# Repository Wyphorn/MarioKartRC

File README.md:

# Mario Kart RC

Mario-Kart-inspiriertes RC-Rennsystem für 8 Fahrzeuge im Außeneinsatz. Die Autos fahren mit ~20 km/h; Items, Kollisionen und Rundenzählung werden automatisch erkannt.

Das Projekt ist auf Nachbau ausgelegt: Alle Bauteile haben eine feste Bestellnummer eines echten Herstellers mit öffentlichem Datenblatt und sind handlötbar (SOT-23, SOT-223, SMA, THT – kein QFN).

---

## Repo-Struktur

| Ordner | Inhalt |
|---|---|
| `fb-firmware/` | Fernbedienung – ESP32-C6-SuperMini, PlatformIO |
| `car-firmware/` | Fahrzeug – ESP32-C6 Mini, PlatformIO |
| `shared/` | Gemeinsamer Code: `mk_protocol.h` (Pakete FB ↔ Auto ↔ Basis), `mk_clock_guard.h` (Workaround für den C6-Uhrenfehler) |
| `kicad/projects/` | KiCad-Projekte je Platine: `kart` (Fahrzeug-Board), `controller` (Fernbedienung), `buttons` (Tasterplatine FB), `switch` (Schalter-Platinchen Kart), jeweils mit Gerber als ZIP |
| `kicad/libs/` | Eigene Symbole und Footprints (`zzzz_Own`, `RF_Module_Own`), von allen Projekten über ihre lokalen Bibliothekstabellen eingebunden |
| `kicad/archive/` | Alte Stände: FB-V1-Layout, erster FB-Schaltplan (D1 Mini, Mai 2026) |
| `docs/` | Weitere Dokumentation, u.a. `base-station.md` |

---

## Gesamtarchitektur

| Bereich | Technologie |
|---|---|
| Drahtlos | ESP-NOW |
| Kabelgebunden | CAN-Bus (STM32F103 + TJA1050) |
| Basisstation | Raspberry Pi 5 + USB-CAN-Adapter |
| Fahrzeugbasis | Carrera 2013 RC-Autos (umgebaut) |
| Fahrzeug-MCU | ESP32-C6 Mini |
| Fernbedienung | ESP32-C6-SuperMini (gleicher Chip wie im Auto) |

**Faustregel:** kabelgebunden = CAN, drahtlos = ESP-NOW.

---

## Betriebs-Modi

**Direct Mode** – Die Fernbedienung (FB) steuert ihr Auto direkt. Keine Basisstation nötig, ideal zum Einzelfahren und Testen.

**Game Mode** – Die FB spricht mit der Basisstation. Diese übernimmt die Spiellogik (Items, Punkte, Kollisionen, Rundenzählung) und leitet die Fahrbefehle ans Auto weiter.

Gewählt wird der Modus mit dem Schiebeschalter der FB: Mitte = Aus, Links = Game, Rechts = Direct.

---

## Kommunikationsprotokoll (`shared/mk_protocol.h`)

Alle ESP-NOW-Pakete beginnen mit einem `uint8_t type` als Unterscheidungsmerkmal.

| Struct | Richtung | Frequenz |
|---|---|---|
| `MK_ControlInput` | FB → Auto (Direct) / FB → Basis (Game) | ~50 Hz |
| `MK_ConfigPacket` | FB → Auto / FB → Basis → Auto | nur bei Änderung |
| `MK_GameFeedback` | Auto → FB (Direct) / Basis → FB (Game) | 5 Hz |
| `MK_Beacon` | FB/Auto → Broadcast | beim Pairing |
| `MK_Assign` | Basis → FB/Auto (Unicast) | beim Pairing |
| `MK_ChannelSwitch` | Basis/FB → Auto | Kanalwechsel / Rennende |
| `MK_Mapping` | Basis → FB/Auto (Unicast) | vor Rennstart |
| `MK_IrConfig` | Basis → Auto (Unicast) | nach Assign (nur Game Mode) |

- **`MK_ControlInput`** – `throttle` und `steering` (–100..100), `buttons` (Bitmaske Gelb/Grün/Blau/Rot), `maxSpeed` (1–10)
- **`MK_ConfigPacket`** – Servo-Trim –10..10; `save = 1` speichert im Auto-EEPROM, `save = 0` ist eine Live-Vorschau
- **`MK_GameFeedback`** – Position, Runde, Item, Rumble, Akkustand des Autos (0–5) und sein aktueller Servo-Trim
- **`MK_Beacon`** – enthält beim Auto die Charakter-ID (1–8)

### Pairing und Wiederverbinden (Direct Mode)

1. Erstes Pairing auf dem Setup-Kanal 1: Das Auto sendet Beacons, die FB antwortet mit `MK_Assign` und schickt es per `MK_ChannelSwitch` auf einen zufälligen Betriebskanal (4, 6, 9 oder 11).
2. Beide speichern Kanal und Gegenstelle im EEPROM.
3. **Wiederverbinden ist FB-gesteuert:** Nach einem Neustart oder Funkabriss meldet sich die FB mit ihrer echten MAC auf dem gespeicherten Kanal beim gespeicherten Auto und sendet einfach Steuerpakete. Das Feedback des Autos bestätigt die Verbindung – kein Beacon, kein erneutes Assign.
4. Rückfall auf Kanal 1 erst, wenn die Gegenstelle wirklich weg ist: Auto nach 30 s Funkstille (5 s direkt nach dem Einschalten), FB nach 30 s (15 s nach dem Einschalten). Kanal 1 wird bewusst vermieden, weil dort die erste FB gewinnt und die Zuordnung FB ↔ Auto wechseln könnte.

---

## Fernbedienung

### Hardware

| Komponente | Details |
|---|---|
| MCU | ESP32-C6-SuperMini (MakerGO) |
| Joysticks | 2× PS2-Analog-Stick, direkt an 3.3V (kein Spannungsteiler) |
| ADC | ADS1115 als Breakout-Modul, I2C 0x48 (ADDR → GND) |
| Display | 1.9" IPS 170×320, ST7789, SPI |
| Buttons | 4× Taster (SNES-Raute) + 2× Stick-Taster (verdrahtet, ohne Funktion) |
| Status-LED | WS2812B, 330 Ω Serienwiderstand |
| Rumble | 2× ERM-Vibrationsmotor 28×12 mm, parallel an Zellspannung |
| Rumble-Treiber | 1× MMBT2222A + 1 kΩ Basis, 1× SS14 Freilaufdiode |
| Akku | 1× 18650, ungeschützt – zum Laden herausnehmen (externes Ladegerät) |
| Verpolschutz | P-MOSFET DMG2301L-7 (Ersatz: DMG2301LK-7), direkt hinter dem Akku |
| Spannungsregler | LDO MCP1826T-3302E/DC, fest 3.3V, 1 A |
| Power/Modus | Schiebeschalter 2P3T: Pol A schaltet SHDN des LDO, Pol B den Modus-Pin |
| Akku-Messung | Teiler 100k/100k + 100 nF an GPIO0 |
| Puffer | 220 µF Elko an der Akkuschiene (Rumble-Anlaufstrom) |

Alle Verbraucher außer dem Rumble laufen an einer einzigen 3.3V-Schiene.

> **Hinweis für Nachbauer:** Auf FB-Board V1 ist die Freilaufdiode D2 im Footprint verdreht. Den Kathodenring entgegen dem Siebdruck auf Pad 2 (+BATT) setzen – das ist die Seite mit Durchgang zu Pin 1 von J6/J7.

### Pinbelegung ESP32-C6-SuperMini

| GPIO | Funktion |
|---|---|
| GPIO0 | ADC – Akku-Messung |
| GPIO1 | Modus-Pin (Game = GND, Direct = 3.3V) |
| GPIO2 | Button Rot |
| GPIO3 | Button Blau |
| GPIO4 | Button Grün |
| GPIO5 | Display MOSI |
| GPIO6 | WS2812B DATA |
| GPIO7 | Display SCK |
| GPIO14 | Display Backlight (PWM) |
| GPIO15 | Display CS |
| GPIO17 | Rumble PWM |
| GPIO18 | Display DC |
| GPIO19 | I2C SDA (ADS1115) |
| GPIO20 | I2C SCL (ADS1115) |
| GPIO21 / 22 | Stick-Taster R / L (inneres Pad, reserviert) |
| GPIO23 | Button Gelb (inneres Pad, einzelner Draht) |

Tabu: GPIO8/9 (Strapping, Onboard-LED/BOOT), GPIO12/13 (USB zum Flashen und für den Serial-Monitor), GPIO16 (UART0 TX, wird vom Boot-ROM getrieben).

ADS1115-Kanäle: A0 = Links X, A1 = Links Y, A2 = Rechts Y, A3 = Rechts X (A2/A3 bewusst getauscht, damit sich die Leitungen nicht kreuzen).

### Tastenbelegung

```
        [Blau]
   [Grün]      [Rot]
        [Gelb]
```

| Taste | Im Menü | Beim Fahren |
|---|---|---|
| Grün | Bestätigen | – |
| Rot | Zurück / Abbrechen | Licht am Auto an/aus |
| Blau | – | Charakter-Sound |
| Gelb | – | – (frei) |
| Grün + Blau 3 s | – | Menü öffnen |
| Rot 10 s halten | – | Einstellungen zurücksetzen (Countdown ab 5 s) |
| Rot beim Einschalten | Einstellungen zurücksetzen | |

Standardbelegung der Sticks: links hoch/runter = Gas, rechts links/rechts = Lenkung (im Menü tauschbar).

### Status-LED

| Farbe | Bedeutung |
|---|---|
| Orange blinkend | sucht Auto bzw. Basis |
| Grün | verbunden |
| Orange | Akku unter 33 % |
| Rot blinkend | Akku unter 16 % |
| Pink | Menü offen |
| Gelb pulsierend / solid | Kalibrierung startet / läuft |

### Einstellungsmenü

| Menüpunkt | Gespeichert |
|---|---|
| Offset-Kalibrierung (Nullpunkt der Sticks) | FB |
| Min/Max-Kalibrierung (8 geführte Schritte) | FB |
| Servo-Trim (±10, Räder bewegen sich live mit, Grün speichert, Rot verwirft) | Auto |
| Max. Speed (1–10) | – |
| Sprache (DE/EN) | FB |
| Rumble an/aus | – |
| Joysticks tauschen | – |
| Debug (Achsen, Buttons, Spannung, Kanal, MAC) | – |
| Reset | – |

Vor der ersten Fahrt **Offset-Kalibrierung** machen – sonst liegt der Nullpunkt der Sticks daneben und das Auto kriecht los.

### Akku

- 0 % = 3.4V, 100 % = 4.2V. Unter ~3.35V fällt der LDO aus der Regelung und die Joystick-Werte wandern – deshalb gilt die Zelle schon bei 3.4V als leer.
- **Tiefentladeschutz:** Liegt die Zelle 30 s unter 3.3V, zeigt die FB „Akku leer – bitte ausschalten“ und geht in Deep Sleep. Nur Aus- und Einschalten holt sie zurück. Ein Restverbrauch von wenigen mA bleibt; bei längerer Lagerung die Zelle herausnehmen.
- Nach 60 s ohne Eingabe wird das Display gedimmt.

---

## Fahrzeug

### Hardware

| Komponente | Details |
|---|---|
| MCU | ESP32-C6 Mini |
| Motortreiber | BTS7960 H-Brücke (IBT-2), 43 A Peak |
| Antrieb | 380er Bürstenmotor, 7.4V, Stallstrom ~8 A |
| Lenkservo | Multiplex MS-12022 MG DIGI, PWM 1050–1950 µs (mechanischer Puffer) |
| Audio | DFPlayer Mini (UART) – Sounds aus einem Ordner pro Charakter |
| IMU | LSM6DS3, I2C 0x6A – Kollisionserkennung |
| LEDs | WS2812B-Kette: Status-LED + 8er-Kreis im Charakterkopf |
| Beleuchtung | Front weiß + Heck rot, Rückfahrlicht weiß |
| IR-Sender | 3× IR-LED 940 nm nach unten (Mitte, ±8 cm) – Typ noch offen |
| Charakter-ID | 4-fach DIP-Schalter + Widerstandsleiter an einem ADC-Pin |
| Akku | 2× 18650 in Serie (2S), ungeschützt – zum Laden herausnehmen |
| Stromversorgung | 7.4V direkt an den BTS7960, 5V über Buck AP63205WU (C6, DFPlayer, LEDs, Servo) |
| Akku-Messung | Teiler 100k/47k an GPIO4 |

### Pinbelegung ESP32-C6 Mini

| GPIO | Funktion |
|---|---|
| GPIO0 | I2C SCL (LSM6DS3) |
| GPIO1 | I2C SDA (LSM6DS3) |
| GPIO2 | ADC – Charakter-ID |
| GPIO3 | IR-LED (über MMBT2222) |
| GPIO4 | ADC – Akku-Messung |
| GPIO5 | BTS7960 RPWM (10k Pulldown) |
| GPIO6 | BTS7960 LPWM (10k Pulldown) |
| GPIO7 | Servo PWM |
| GPIO14 | Rückfahrlicht |
| GPIO15 | Front- + Rücklicht |
| GPIO18 | UART1 TX → DFPlayer RX |
| GPIO19 | UART1 RX ← DFPlayer TX |
| GPIO20 | WS2812B DATA |

BTS7960 R_EN/L_EN fest an 5V. GPIO8/9 bleiben frei (Strapping: dürfen beim Reset nicht auf LOW gezogen werden).

### Charakter-Identifikation (DIP-Schalter)

10 kΩ nach 3.3V, dazu vier Widerstände (4.7k / 10k / 20k / 51k), je per DIP-Schalter nach GND. Der kleinste Abstand zwischen zwei Charakteren beträgt 254 mV.

| Charakter | DIP [4.7k 10k 20k 51k] | Spannung | SD-Ordner |
|---|---|---|---|
| Mario    | 1110 | 0.713V | 01 |
| Luigi    | 1000 | 1.055V | 02 |
| Yoshi    | 0110 | 1.320V | 03 |
| Bowser   | 0100 | 1.650V | 04 |
| DK       | 0011 | 1.946V | 05 |
| Peach    | 0010 | 2.200V | 06 |
| Toad     | 0001 | 2.759V | 07 |
| Rosalina | 0000 | 3.300V | 08 |

Wird der DIP-Schalter umgestellt, während das Auto nicht verbunden ist, spielt es zur Kontrolle den Erkennungssound des neuen Charakters.

### SD-Karte des DFPlayers

```
/01/  001.mp3, 002.mp3, …   ← Mario
/02/  …                     ← Luigi
…
/08/  …                     ← Rosalina
/09/  …                     ← Spiel-Sounds (Stern, Banane, …)
```

Welche Tracks fröhlich bzw. traurig sind, steht in den Arrays `kJoy_*` / `kSad_*` am Anfang von `car-firmware/src/main.cpp`.

### LEDs

| Index | Funktion |
|---|---|
| 0 | Status-LED |
| 1–8 | Charakter-Kreis (Regenbogen) |

| Status-LED | Bedeutung |
|---|---|
| Orange blinkend | sucht / Verbindung unterbrochen |
| Grün | verbunden |
| Gelb | Akku unter 3.3V/Zelle |
| Rot blinkend | Akku unter 3.2V/Zelle – Abschaltung steht bevor |

### Akku

**Tiefentladeschutz:** Liegt der Akku 30 s unter 6.4V (3.2V/Zelle), stoppt das Auto, spielt einen traurigen Sound und geht in Deep Sleep. Jede Messung zählt, auch unter Last; eine erholte Messung beim Gaswegnehmen setzt den Zähler zurück. So löst es im Rennen erst aus, wenn der Akku wirklich leer ist.

### Kollisionserkennung

LSM6DS3 im ±16g-Bereich. Bei einem Stoß über der Schwelle vibriert die gekoppelte FB 2 s lang, danach 3 s Pause. Die Schwelle steht zum Testen auf 1.5g und soll nach dem Fahrtest wieder auf ~6g.

---

## Firmware bauen und flashen

```bash
cd fb-firmware      # bzw. car-firmware
pio run -t upload
pio device monitor
```

`upload_port`/`monitor_port` in `platformio.ini` sind auf die Seriennummern der eigenen Boards festgelegt – für andere Boards anpassen oder entfernen. Geflasht wird über den eingebauten USB-Port des C6 (USB-Serial/JTAG).

Beide Firmwares nutzen eine OTA-taugliche Partitionstabelle (`default.csv`). Sie lässt sich nur per USB ändern, deshalb ist sie ab dem ersten Flash gesetzt.

### ESP32-C6 rev v0.2: Uhr springt zurück

Beim ESP32-C6 in Revision v0.2 fallen im Zeitgeber gelegentlich einzelne Bits aus, sobald Funk und ein I2C-Master gleichzeitig laufen – `millis()` springt dann um Sekunden bis Minuten zurück ([esp-idf #19036](https://github.com/espressif/esp-idf/issues/19036)). Die Firmware umgeht das mit `shared/mk_clock_guard.h`:

- `nowMs()` zählt über den FreeRTOS-Tick, der auf einem nicht betroffenen Zähler läuft. Im eigenen Code **immer `nowMs()` statt `millis()` verwenden.**
- Ein Guard-Task erkennt Rücksprünge und setzt die Systemuhr zurück auf Stand (Log-Zeile `[CLOCK]`).
- Der WLAN-Stromsparmodus ist abgeschaltet.

Die Revision zeigt `esptool.py chip_id` an.

---

## Streckeninfrastruktur und IR-System

| Komponente | Funktion |
|---|---|
| TSOP38238 | IR-Empfänger, 38 kHz, ±45° – in Toren und Bodenplatten |
| STM32F103 + TJA1050 | CAN-Controller + Transceiver in den Tor-Nodes |
| RPi 5 + USB-CAN | Basisstation / Spielserver |

**Weg eines Ereignisses:** Auto fährt über eine Bodenplatte → TSOP38238 erkennt die IR-ID → STM32 → CAN → RPi 5 → Spiellogik.

Pro Tor sitzen drei Empfänger (Mitte und ±8 cm) passend zu den drei IR-LEDs am Auto. Bei 20 km/h bleibt ein Erkennungsfenster von ~8 ms.

---

## Projektstatus

| Schritt | Status |
|---|---|
| Architektur, Komponentenwahl, Protokoll | ✅ |
| Auto-Firmware (ESP-NOW, Motor, Servo, LEDs, IMU, Sound, Akku-Schutz) | ✅ |
| FB-Firmware auf ESP32-C6 portiert (Display, Menü, ESP-NOW, Rumble, Akku-Schutz) | ✅ |
| Direct Mode Ende-zu-Ende (Pairing, Reconnect, Trim, Sound, Licht) | ✅ |
| KiCad: Kart-Board und FB-Board | ✅ |
| FB-Board V1 gefertigt und aufgebaut | ✅ |
| Race-Display (Charakter, Position, Runde, Item) | ⏳ |
| IR-LED auswählen, einbauen, 38-kHz-Modulation | ⏳ |
| Verpolschutz + Hauptschalter am Akkuhalter des Autos | ⏳ |
| FB-Board V2 (Diode gedreht, Basis-Pulldown, 0.5-mm²-Anschlüsse) | ⏳ |
| Gehäuse anpassen (Fusion 360) | ⏳ |
| Basisstation-Software (Raspberry Pi) | ⏳ |
| Game Mode Ende-zu-Ende | ⏳ |
| OTA-Update | ⏳ zurückgestellt bis nach den ersten Fahrten |

---

## Verworfene Optionen

| Option | Grund |
|---|---|
| UWB für Positionierung | zu komplex |
| MAX98357A (I2S) für den Sound im Auto | DFPlayer Mini ist einfacher |
| DRV8833 als Motortreiber | max. 1.5 A gegen 8 A Stallstrom |
| IRFZ44N / RFP30N06LE für den Rumble | nicht Logic-Level bzw. zu groß |
| Piezo-Buzzer in der FB | kein Sound in der FB |
| D1 Mini (ESP8266) für die FB | ersetzt durch ESP32-C6: ein Chip-Typ für Auto und FB, Hardware-SPI fürs Display, einheitliches OTA |
| OLED (SSD1306/SSD1309) in der FB | ungünstiges Seitenverhältnis; stattdessen 1.9" IPS |
| Battery Shield / Buck-Boost für die FB | LDO genügt, die Schiene muss nur unter 3.6V bleiben; Buck-Boost-ICs waren QFN oder zu schwach |
| AMS1117 / LD1117 als FB-Regler | 1.1–1.3V Dropout – an einer 18650 unbrauchbar |
| 2 Zellen in der FB | konstruktiv ausgeschlossen |
| VSMA1094750X02 als IR-Sender | ±75° passt nicht zu den ±45° des TSOP38238 |

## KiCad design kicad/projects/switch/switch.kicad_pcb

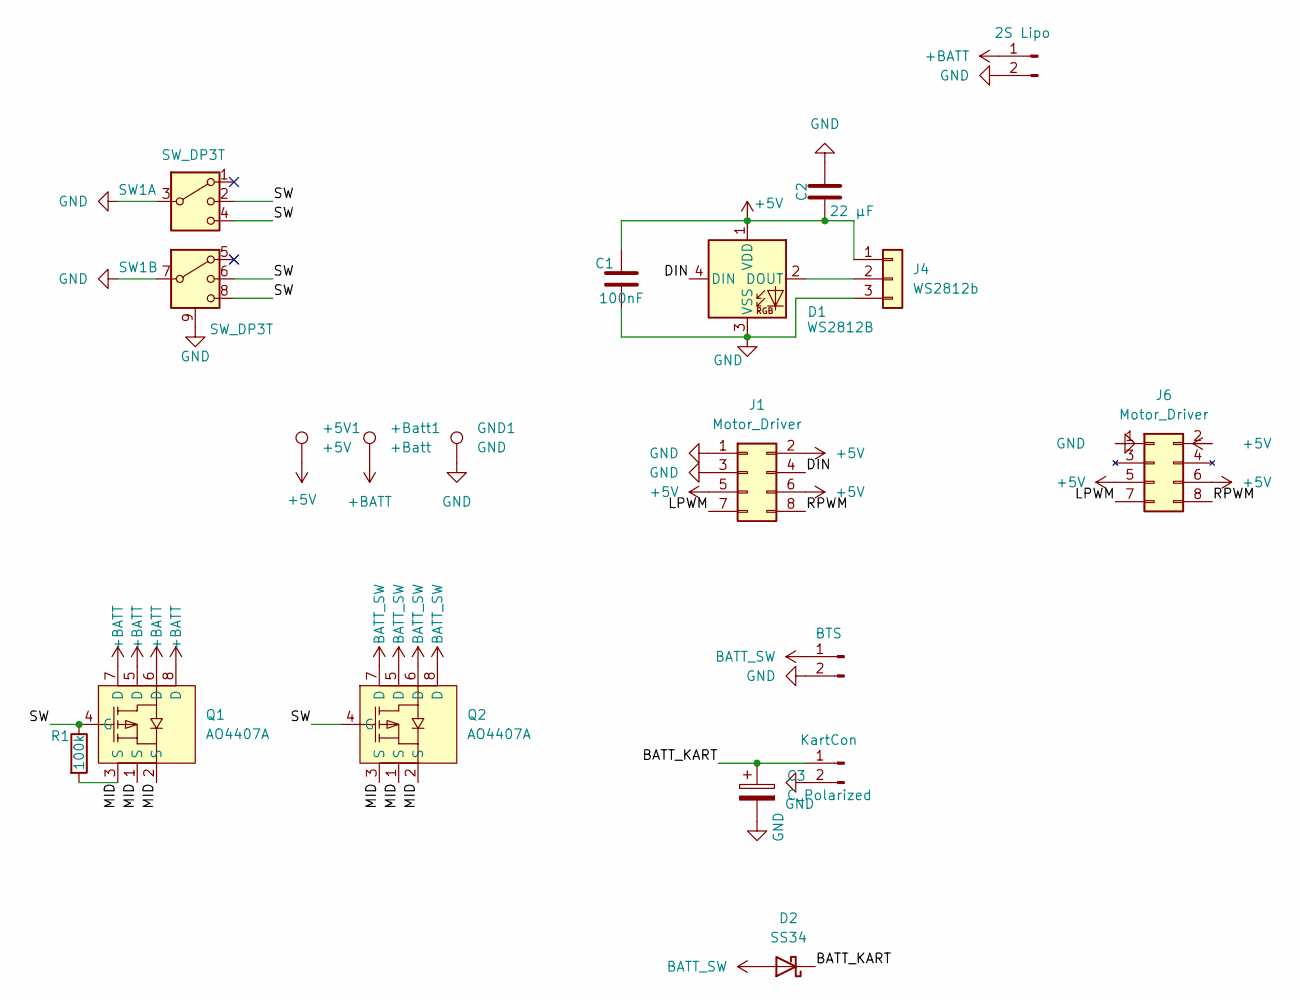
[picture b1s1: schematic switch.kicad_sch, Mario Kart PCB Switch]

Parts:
+5V1: +5V; TestPoint_Pad_D2.0mm
+Batt1: +Batt; TestPoint_Pad_D2.0mm
C1: 100nF; C_0805_2012Metric_Pad1.18x1.45mm_HandSolder
C2: 22 µF; C_1206_3216Metric
C3: C_Polarized; CP_Elec_12.5x13.5
D1: WS2812B; LED_WS2812B_PLCC4_5.0x5.0mm_P3.2mm
D2: SS34; D_SMA
GND1: GND; TestPoint_Pad_D2.0mm
J1: Motor_Driver; IDC-Header_2x04_P2.54mm_Vertical
J2: BTS; Pins_1x02_P5.0mm_D1.4mm_OD3.0mm
J3: KartCon; SolderWire-0.75sqmm_1x02_P4.8mm_D1.25mm_OD2.3mm
J4: WS2812b; PinHeader_1x03_P2.54mm_Vertical
J5: 2S Lipo; SolderWire-0.75sqmm_1x02_P4.8mm_D1.25mm_OD2.3mm
J6: Motor_Driver; PinSocket_2x04_P2.54mm_Vertical
Q1, Q2: AO4407A; SOIC-8_L4.9-W3.9-P1.27-LS6.0-BL; MPN AO4407A; LCSC Part C16072
R1: 100k; R_0805_2012Metric_Pad1.20x1.40mm_HandSolder
SW1: SW_DP3T; SW_Slide_2P3T_8pin_P2.0mm_MountingLugs

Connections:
+5V: +5V1.1 (1_1), C1.1, C2.1, D1.1 (VDD), J1.2, J1.5, J1.6, J4.1, J6.2, J6.5, J6.6
+BATT: +Batt1.1 (1_1), J5.1, Q1.5 (D), Q1.6 (D), Q1.7 (D), Q1.8 (D)
/BATT_KART: C3.1, D2.1 (K), J3.1
/DIN: D1.4 (DIN), J1.4
/LPWM: J1.7, J6.7
/MID: Q1.1 (S), Q1.2 (S), Q1.3 (S), Q2.1 (S), Q2.2 (S), Q2.3 (S), R1.2
/RPWM: J1.8, J6.8
/SW: Q1.4 (G), Q2.4 (G), R1.1, SW1.2, SW1.4, SW1.6, SW1.8
BATT_SW: D2.2 (A), J2.1, Q2.5 (D), Q2.6 (D), Q2.7 (D), Q2.8 (D)
GND: C1.2, C2.2, C3.2, D1.3 (VSS), GND1.1 (1_1), J1.1, J1.3, J2.2, J3.2, J4.3, J5.2, J6.1, SW1.3, SW1.7, SW1.9 (GND)
unnamed: D1.2 (DOUT), J4.2

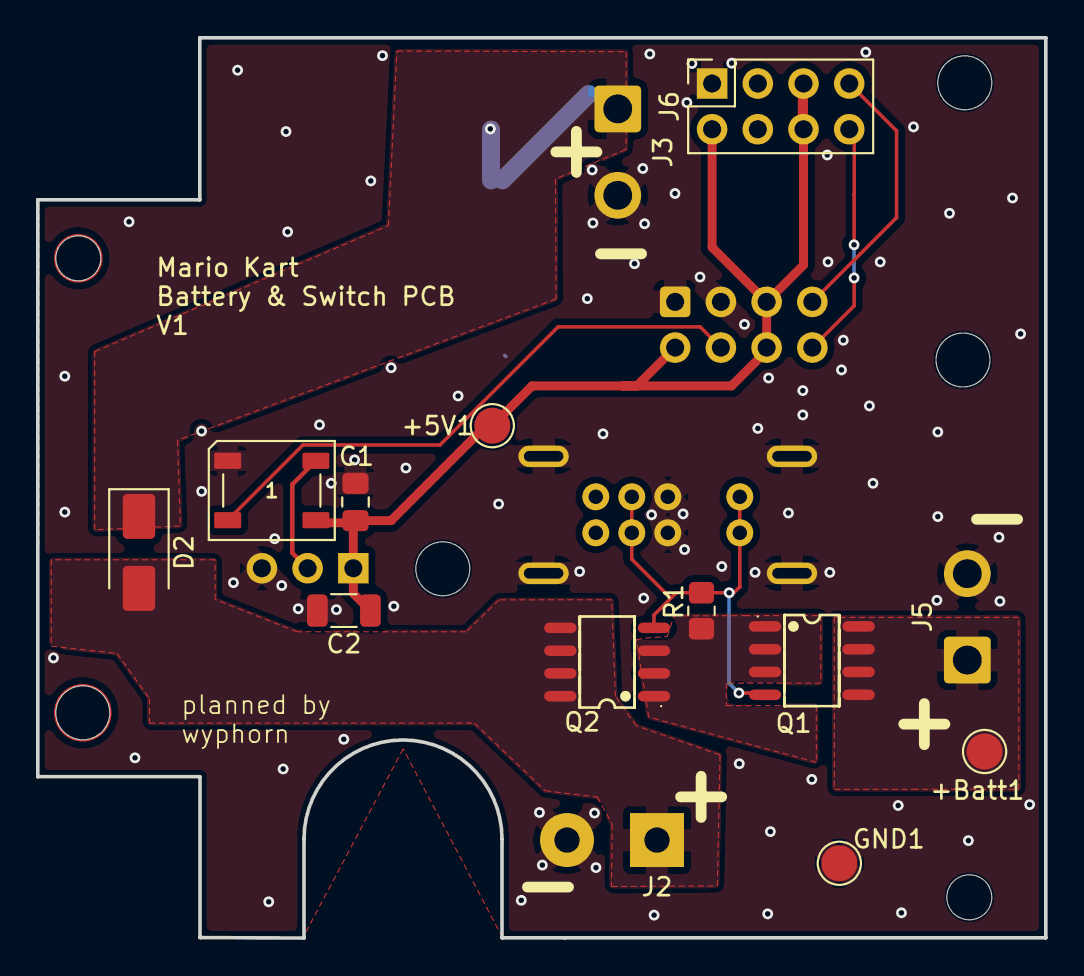
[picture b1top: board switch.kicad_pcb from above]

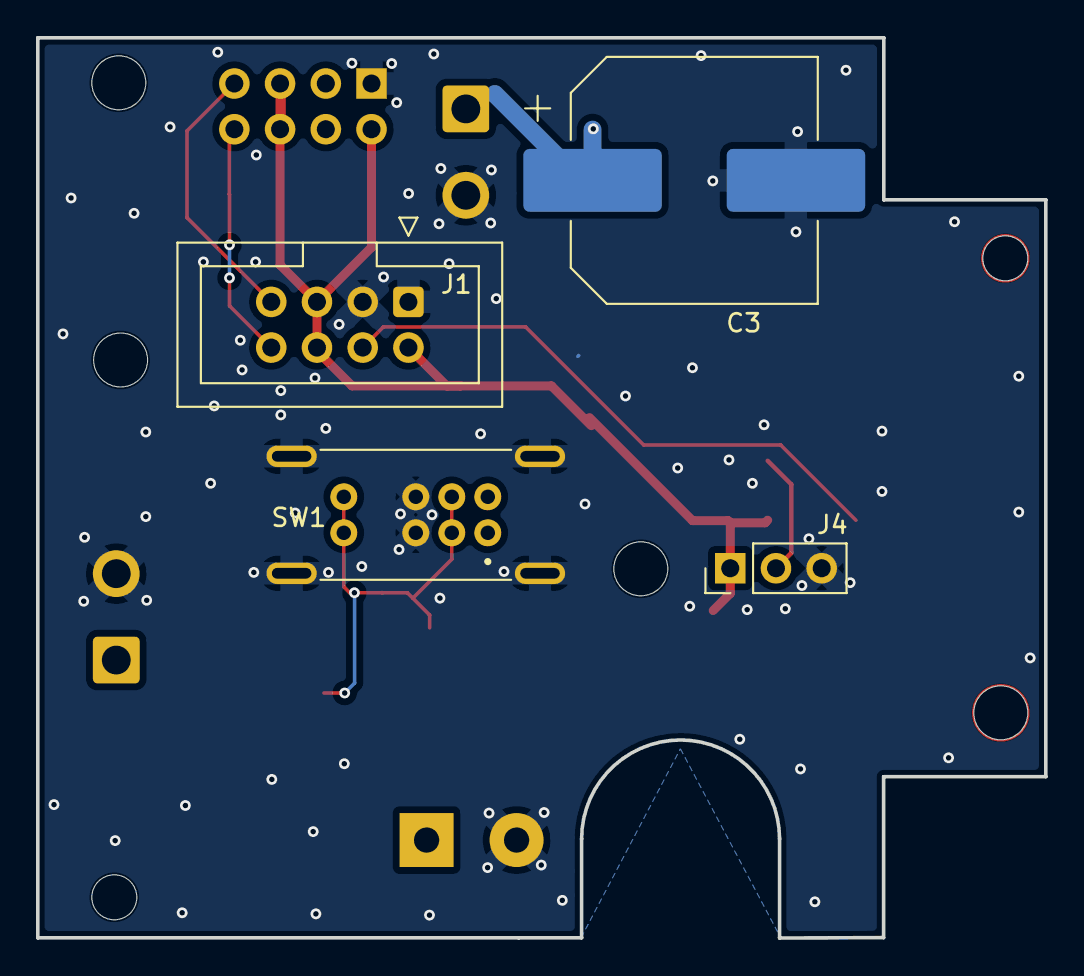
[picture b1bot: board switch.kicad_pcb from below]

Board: 2 copper layers, 56.0 x 50.0 mm, 20 parts (4 on the bottom side), 11 nets.

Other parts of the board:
H1, H2: MountingHole_3mm

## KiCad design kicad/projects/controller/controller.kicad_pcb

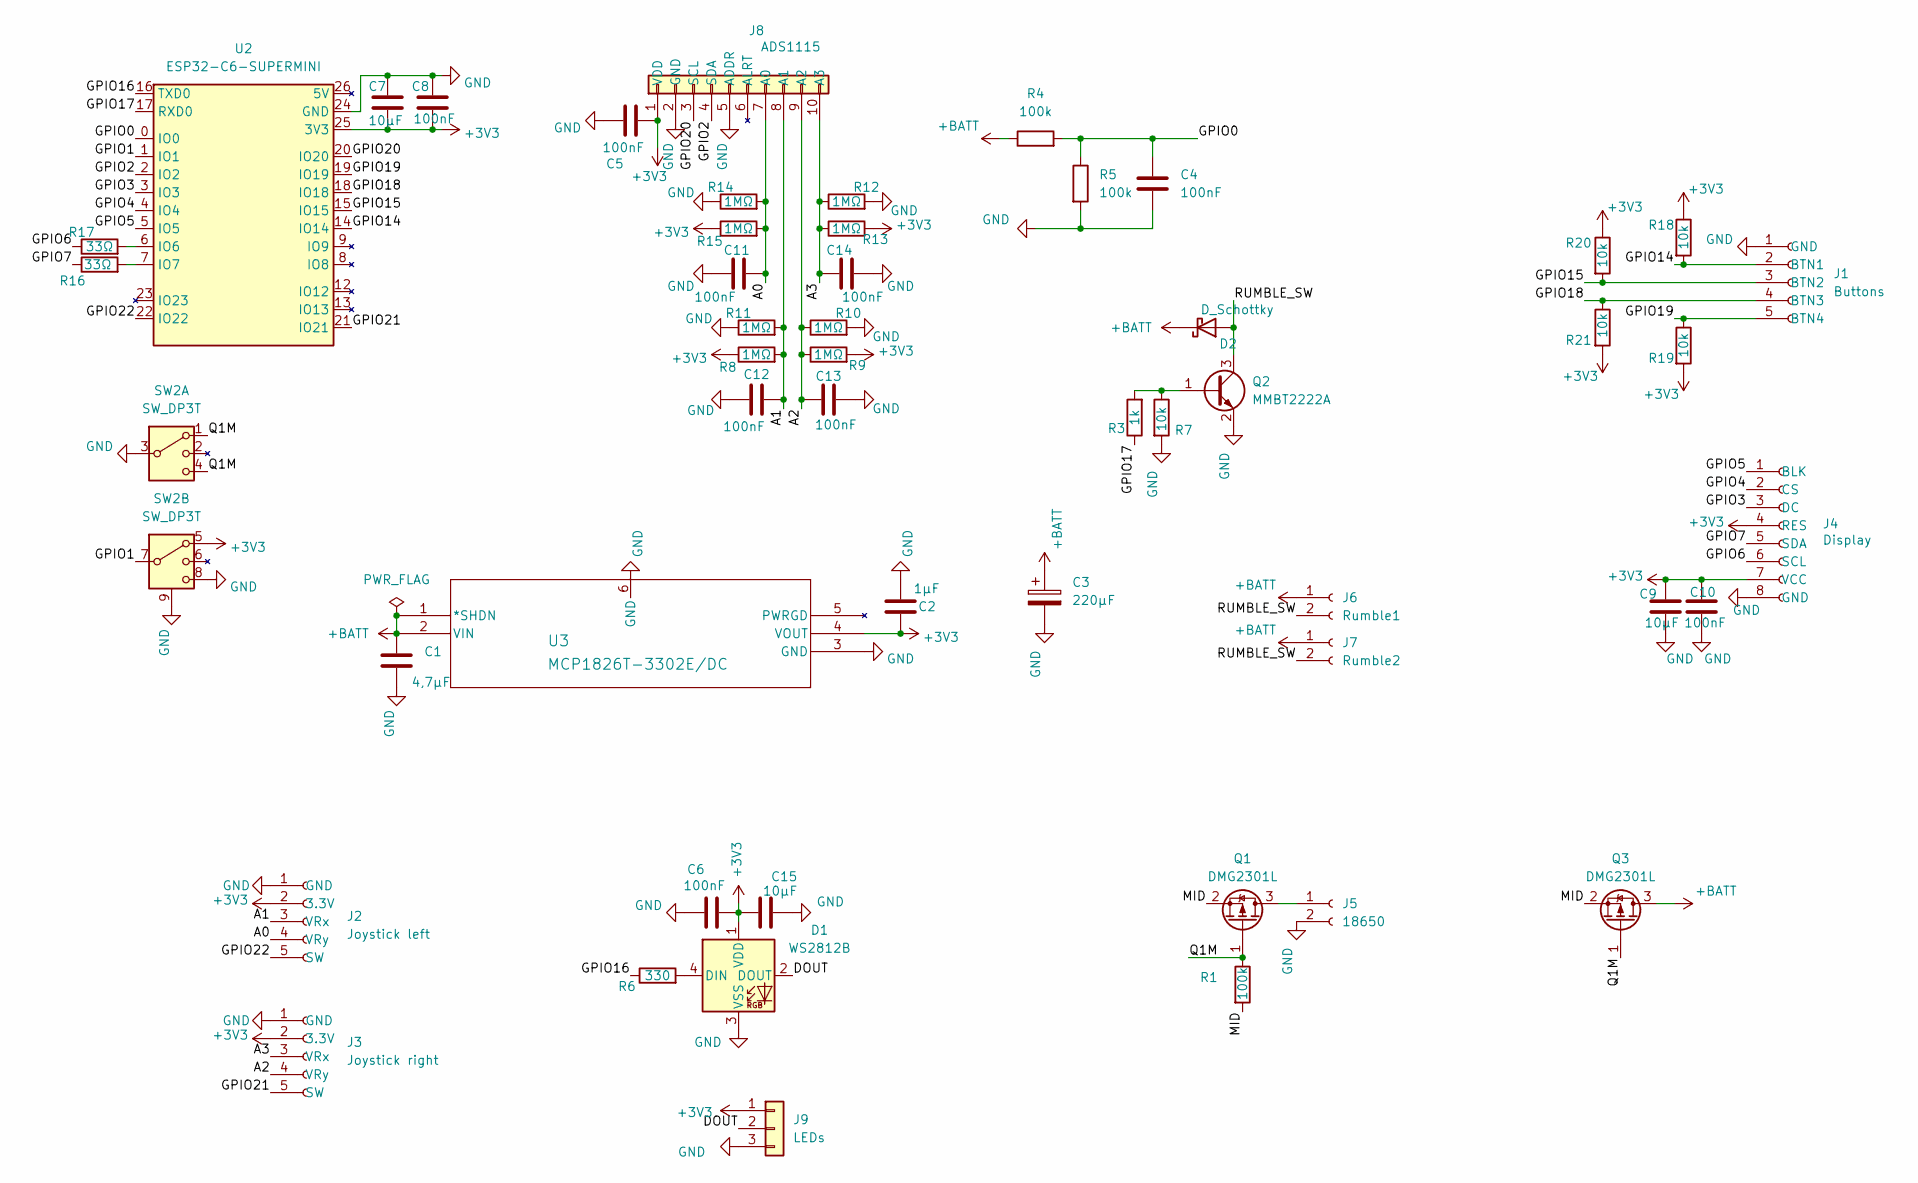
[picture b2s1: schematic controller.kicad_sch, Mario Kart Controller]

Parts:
C1: 4,7µF; C_0805_2012Metric_Pad1.18x1.45mm_HandSolder
C2: 1µF; C_0805_2012Metric_Pad1.18x1.45mm_HandSolder
C3: 220µF; CP_Elec_6.3x5.4
C4, C5, C6, C8, C10, C11, C12, C13, C14: 100nF; C_0805_2012Metric_Pad1.18x1.45mm_HandSolder
C7, C9, C15: 10µF; C_1206_3216Metric_Pad1.33x1.80mm_HandSolder
D1: WS2812B; LED_WS2812B_PLCC4_5.0x5.0mm_P3.2mm
D2: D_Schottky; D_SMA_Handsoldering
J1: Buttons; PinHeader_1x05_P2.54mm_Vertical
J2: Joystick left; JST_XH_S5B-XH-A-1_1x05_P2.50mm_Horizontal
J3: Joystick right; JST_XH_S5B-XH-A-1_1x05_P2.50mm_Horizontal
J4: Display; JST_XH_S8B-XH-A-1_1x08_P2.50mm_Horizontal
J5: 18650; SolderWire-0.75sqmm_1x02_P4.8mm_D1.25mm_OD2.3mm
J6: Rumble1; PinHeader_1x02_P2.54mm_Vertical
J7: Rumble2; PinHeader_1x02_P2.54mm_Vertical
J8: ADS1115; PinHeader_1x10_P2.54mm_Vertical
J9: LEDs; PinHeader_1x03_P2.54mm_Vertical
Q1, Q3: DMG2301L; SOT-23_Handsoldering
Q2: MMBT2222A; SOT-23_Handsoldering
R1, R4, R5: 100k; R_0805_2012Metric_Pad1.20x1.40mm_HandSolder
R3: 1k; R_0805_2012Metric_Pad1.20x1.40mm_HandSolder
R6: 330; R_0805_2012Metric_Pad1.20x1.40mm_HandSolder
R7, R18, R19, R20, R21: 10k; R_0805_2012Metric_Pad1.20x1.40mm_HandSolder
R8, R9, R10, R11, R12, R13, R14, R15: 1MΩ; R_0805_2012Metric_Pad1.20x1.40mm_HandSolder
R16, R17: 33Ω; R_0805_2012Metric_Pad1.20x1.40mm_HandSolder
SW2: SW_DP3T; SW_Slide_2P3T_8pin_P2.0mm_MountingLugs
U2: ESP32-C6-SUPERMINI; ESP32-C6-SuperMini_2x10_P2.54mm_Row15.24mm
U3: MCP1826T-3302E/DC; SOT-223_5MC_MCH

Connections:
+3V3: C2.1, C5.1, C6.1, C7.2, C8.2, C9.1, C10.1, C15.1, D1.1 (VDD), J2.2 (3.3V), J3.2 (3.3V), J4.4 (RES), J4.7 (VCC), J8.1 (VDD), J9.1, R8.1, R9.2, R13.2, R15.1, R18.1, R19.2, R20.1, R21.2, SW2.5, U2.25 (3V3), U3.4 (VOUT)
+BATT: C1.1, C3.1, D2.1 (K), J6.1, J7.1, Q3.3 (D), R4.1, U3.1 (*SHDN), U3.2 (VIN)
/A0: C11.2, J2.4 (VRy), J8.7 (A0), R14.2, R15.2
/A1: C12.1, J2.3 (VRx), J8.8 (A1), R8.2, R11.2
/A2: C13.1, J3.4 (VRy), J8.9 (A2), R9.1, R10.1
/A3: C14.1, J3.3 (VRx), J8.10 (A3), R12.1, R13.1
/DOUT: D1.2 (DOUT), J9.2
/GPIO0: C4.1, R4.2, R5.1, U2.0 (IO0)
/GPIO1: SW2.7, U2.1 (IO1)
/GPIO2: J8.4 (SDA), U2.2 (IO2)
/GPIO3: J4.3 (DC), U2.3 (IO3)
/GPIO4: J4.2 (CS), U2.4 (IO4)
/GPIO5: J4.1 (BLK), U2.5 (IO5)
/GPIO6: J4.6 (SCL), R17.1
/GPIO7: J4.5 (SDA), R16.1
/GPIO14: J1.2 (BTN1), R18.2, U2.14 (IO14)
/GPIO15: J1.3 (BTN2), R20.2, U2.15 (IO15)
/GPIO16: R6.1, U2.16 (TXD0)
/GPIO17: R3.1, U2.17 (RXD0)
/GPIO18: J1.4 (BTN3), R21.1, U2.18 (IO18)
/GPIO19: J1.5 (BTN4), R19.1, U2.19 (IO19)
/GPIO20: J8.3 (SCL), U2.20 (IO20)
/GPIO21: J3.5 (SW), U2.21 (IO21)
/GPIO22: J2.5 (SW), U2.22 (IO22)
/MID: Q1.2 (S), Q3.2 (S), R1.2
/Q1M: Q1.1 (G), Q3.1 (G), R1.1, SW2.1, SW2.4
/RUMBLE_SW: D2.2 (A), J6.2, J7.2, Q2.3 (C)
GND: C1.2, C2.2, C3.2, C4.2, C5.2, C6.2, C7.1, C8.1, C9.2, C10.2, C11.1, C12.2, C13.2, C14.2, C15.2, D1.3 (VSS), J1.1 (GND), J2.1 (GND), J3.1 (GND), J4.8 (GND), J5.2, J8.2 (GND), J8.5 (ADDR), J9.3, Q2.2 (E), R5.2, R7.2, R10.2, R11.1, R12.2, R14.1, SW2.3, SW2.8, SW2.9 (GND), U2.24 (GND), U3.3 (GND), U3.6 (GND)
unnamed: D1.4 (DIN), R6.2
unnamed: J5.1, Q1.3 (D)
unnamed: Q2.1 (B), R3.2, R7.1
unnamed: R17.2, U2.6 (IO6)
unnamed: R16.2, U2.7 (IO7)

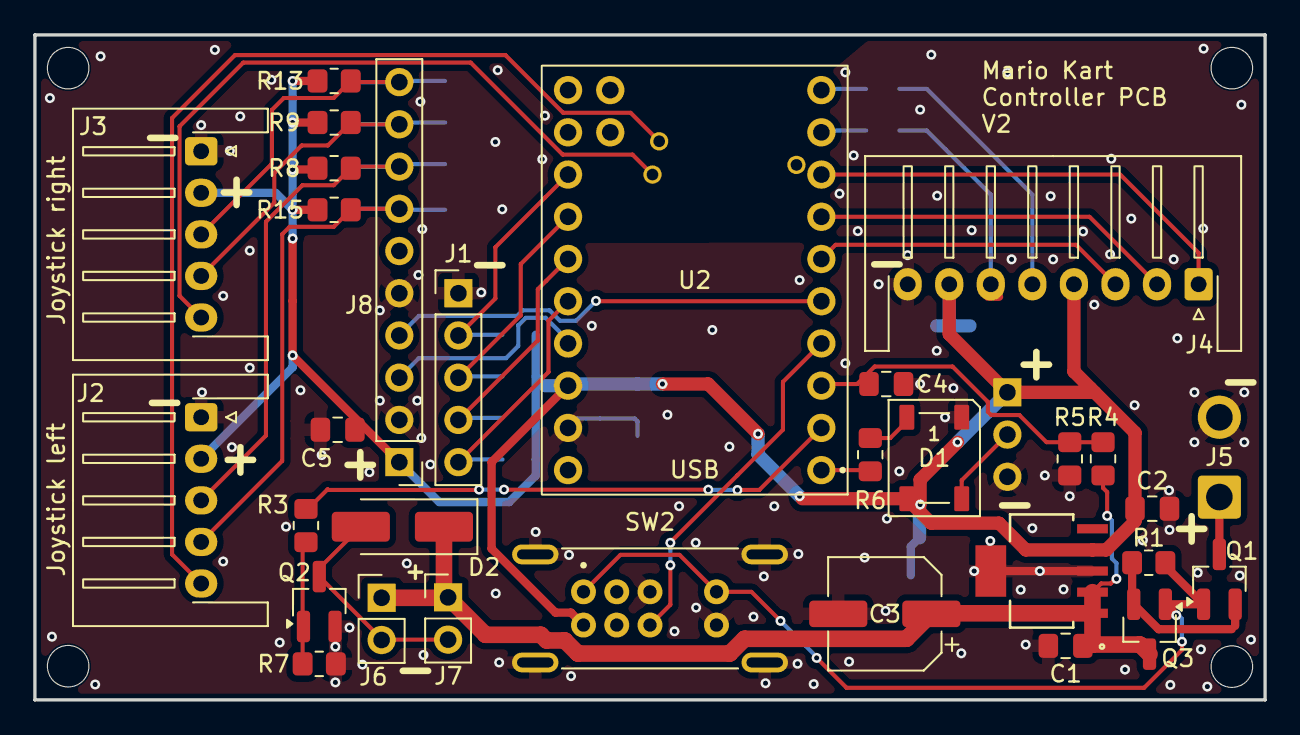
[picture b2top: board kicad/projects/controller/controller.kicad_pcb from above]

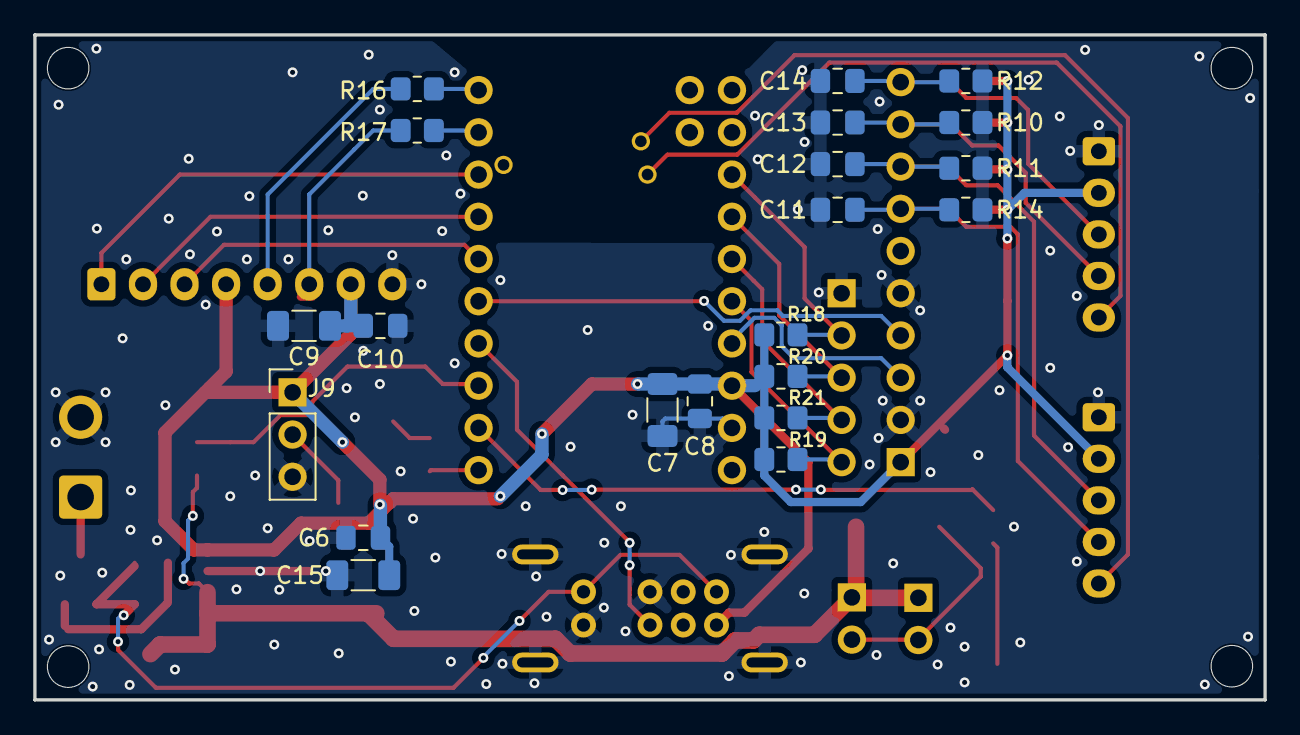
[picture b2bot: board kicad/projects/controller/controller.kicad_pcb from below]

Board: 2 copper layers, 74.0 x 40.0 mm, 52 parts (21 on the bottom side), 33 nets.

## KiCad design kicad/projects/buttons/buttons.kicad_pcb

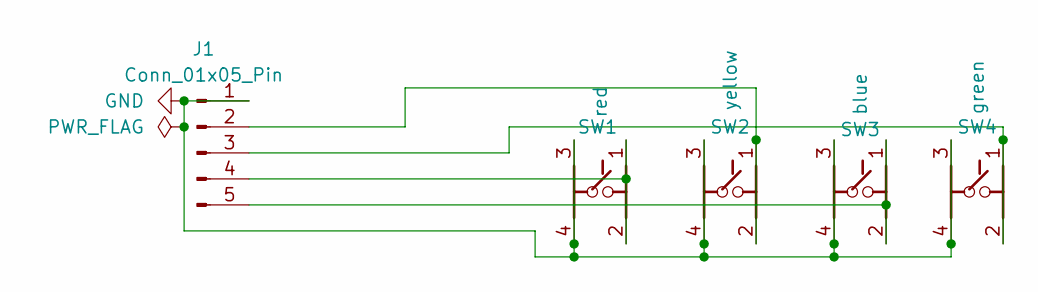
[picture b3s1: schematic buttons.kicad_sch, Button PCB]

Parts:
J1: Conn_01x05_Pin; JST_XH_S5B-XH-A-1_1x05_P2.50mm_Horizontal
SW1: red; SW_Tactile_12x12mm_THT_P12.5x5.0mm
SW2: yellow; SW_Tactile_12x12mm_THT_P12.5x5.0mm
SW3: blue; SW_Tactile_12x12mm_THT_P12.5x5.0mm
SW4: green; SW_Tactile_12x12mm_THT_P12.5x5.0mm

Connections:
GND: J1.1, SW1.3, SW1.4, SW2.3, SW2.4, SW3.3, SW3.4, SW4.3, SW4.4
unnamed: J1.2, SW2.1, SW2.2
unnamed: J1.3, SW4.1, SW4.2
unnamed: J1.4, SW1.1, SW1.2
unnamed: J1.5, SW3.1, SW3.2

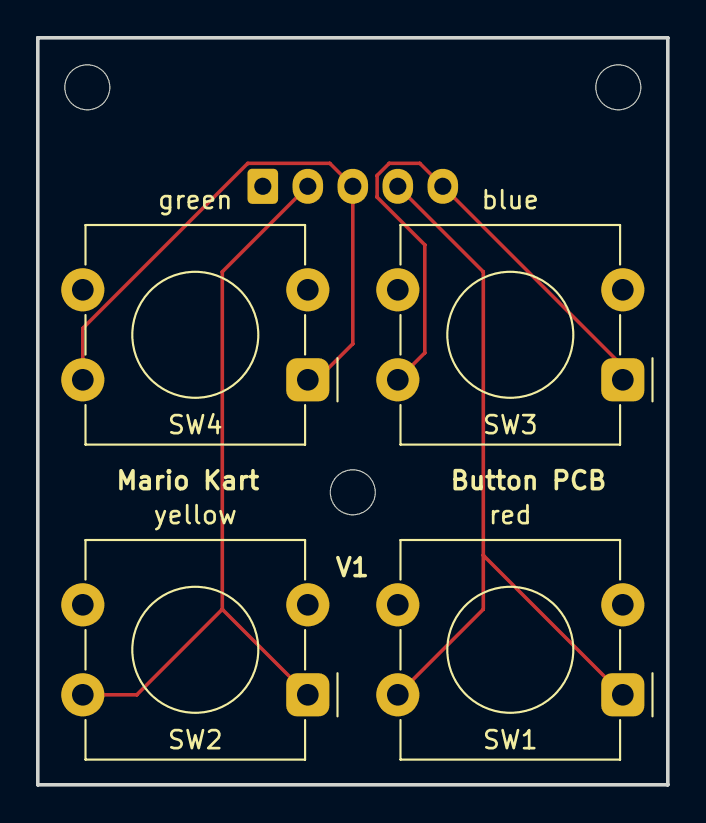
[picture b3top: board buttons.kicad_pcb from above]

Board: 2 copper layers, 35.0 x 41.5 mm, 5 parts (1 on the bottom side), 5 nets.

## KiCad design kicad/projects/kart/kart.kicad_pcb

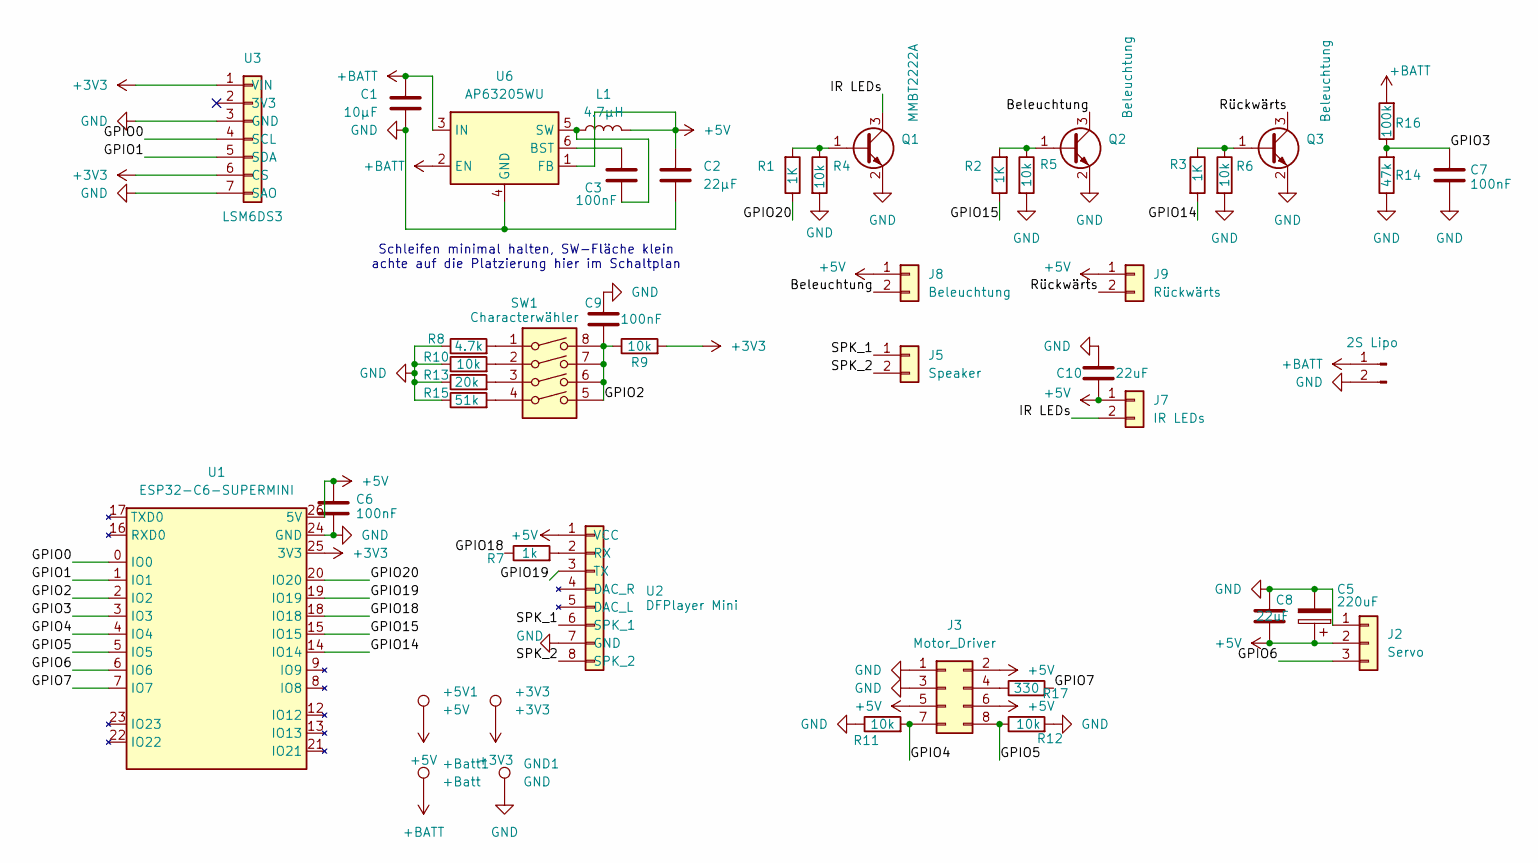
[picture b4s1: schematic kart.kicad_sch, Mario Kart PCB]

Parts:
+3V3: +3V3; TestPoint_Pad_D2.0mm
+5V1: +5V; TestPoint_Pad_D2.0mm
+Batt1: +Batt; TestPoint_Pad_D2.0mm
C1: 10µF; C_1206_3216Metric_Pad1.33x1.80mm_HandSolder
C2: 22µF; C_1206_3216Metric_Pad1.33x1.80mm_HandSolder
C3, C6, C7, C9: 100nF; C_0805_2012Metric_Pad1.18x1.45mm_HandSolder
C5: 220uF; CP_Elec_6.3x5.4
C8, C10: 22uF; C_1206_3216Metric_Pad1.33x1.80mm_HandSolder
GND1: GND; TestPoint_Pad_D2.0mm
J2: Servo; JST_XH_B3B-XH-A_1x03_P2.50mm_Vertical
J3: Motor_Driver; IDC-Header_2x04_P2.54mm_Vertical
J4: 2S Lipo; SolderWire-0.75sqmm_1x02_P4.8mm_D1.25mm_OD2.3mm
J5: Speaker; PinHeader_1x02_P2.54mm_Vertical
J7: IR LEDs; PinHeader_1x02_P2.54mm_Vertical
J8: Beleuchtung; PinHeader_1x02_P2.54mm_Vertical
J9: Rückwärts; PinHeader_1x02_P2.54mm_Vertical
L1: 4.7µH; L_Bourns_SRN6045TA
Q1: MMBT2222A; SOT-23_Handsoldering
Q2, Q3: Beleuchtung; SOT-23_Handsoldering
R1, R2, R3: 1K; R_0805_2012Metric_Pad1.20x1.40mm_HandSolder
R4, R5, R6, R9, R10, R11, R12: 10k; R_0805_2012Metric_Pad1.20x1.40mm_HandSolder
R7: 1k; R_0805_2012Metric_Pad1.20x1.40mm_HandSolder
R8: 4.7k; R_0805_2012Metric_Pad1.20x1.40mm_HandSolder
R13: 20k; R_0805_2012Metric_Pad1.20x1.40mm_HandSolder
R14: 47k; R_0805_2012Metric_Pad1.20x1.40mm_HandSolder
R15: 51k; R_0805_2012Metric_Pad1.20x1.40mm_HandSolder
R16: 100k; R_0805_2012Metric_Pad1.20x1.40mm_HandSolder
R17: 330; R_0805_2012Metric_Pad1.20x1.40mm_HandSolder
SW1: Characterwähler; SW_DIP_SPSTx04_Piano_10.8x11.72mm_W7.62mm_P2.54mm
U1: ESP32-C6-SUPERMINI; ESP32-C6-SuperMini_2x10_P2.54mm_Row15.24mm
U2: DFPlayer Mini; PinHeader_1x08_P2.54mm_Vertical
U3: LSM6DS3; PinHeader_1x07_P2.54mm_Vertical
U6: AP63205WU; TSOT-23-6

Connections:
+3V3: +3V3.1 (1_1), R9.2, U1.25 (3V3), U3.1 (VIN), U3.6 (CS)
+5V: +5V1.1, C2.1, C5.1, C6.1, C8.2, C10.2, J2.2, J3.2, J3.5, J3.6, J7.1, J8.1, J9.1, L1.2, U1.26 (5V), U2.1 (VCC), U6.1 (FB); also elsewhere on the board
+BATT: +Batt1.1, C1.1, J4.1, R16.2, U6.2 (EN), U6.3 (IN); also elsewhere on the board
/Beleuchtung: J8.2, Q2.3 (C)
/GPIO0: U1.0 (IO0), U3.4 (SCL)
/GPIO1: U1.1 (IO1), U3.5 (SDA)
/GPIO2: C9.2, R9.1, SW1.5, SW1.6, SW1.7, SW1.8, U1.2 (IO2)
/GPIO3: C7.1, R14.2, R16.1, U1.3 (IO3)
/GPIO4: J3.7, R11.2, U1.4 (IO4)
/GPIO5: J3.8, R12.1, U1.5 (IO5)
/GPIO6: J2.3, U1.6 (IO6)
/GPIO7: R17.2, U1.7 (IO7)
/GPIO14: R3.2, U1.14 (IO14)
/GPIO15: R2.1, U1.15 (IO15)
/GPIO18: R7.1, U1.18 (IO18)
/GPIO19: U1.19 (IO19), U2.3 (TX)
/GPIO20: R1.1, U1.20 (IO20)
/IR LEDs: J7.2, Q1.3 (C)
/Rückwärts: J9.2, Q3.3 (C)
/SPK_1: J5.1, U2.6 (SPK_1)
/SPK_2: J5.2, U2.8 (SPK_2)
GND: C1.2, C2.2, C5.2, C6.2, C7.2, C8.1, C9.1, C10.1, GND1.1, J2.1, J3.1, J3.3, J4.2, Q1.2 (E), Q2.2 (E), Q3.2 (E), R4.2, R5.2, R6.2, R8.1, R10.1, R11.1, R12.2, R13.1, R14.1, R15.1, U1.24 (GND), U2.7 (GND), U3.3 (GND), U3.7 (SAO), U6.4 (GND); also elsewhere on the board
unnamed: J3.4, R17.1
unnamed: Q1.1 (B), R1.2, R4.1
unnamed: Q2.1 (B), R2.2, R5.1
unnamed: Q3.1 (B), R3.1, R6.1
unnamed: R8.2, SW1.1
unnamed: R10.2, SW1.2
unnamed: R13.2, SW1.3
unnamed: R15.2, SW1.4
unnamed: R7.2, U2.2 (RX)
unnamed: C3.1, U6.6 (BST)
unnamed: C3.2, L1.1, U6.5 (SW)

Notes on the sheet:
Schleifen minimal halten, SW-Fläche klein achte auf die Platzierung hier im Schaltplan

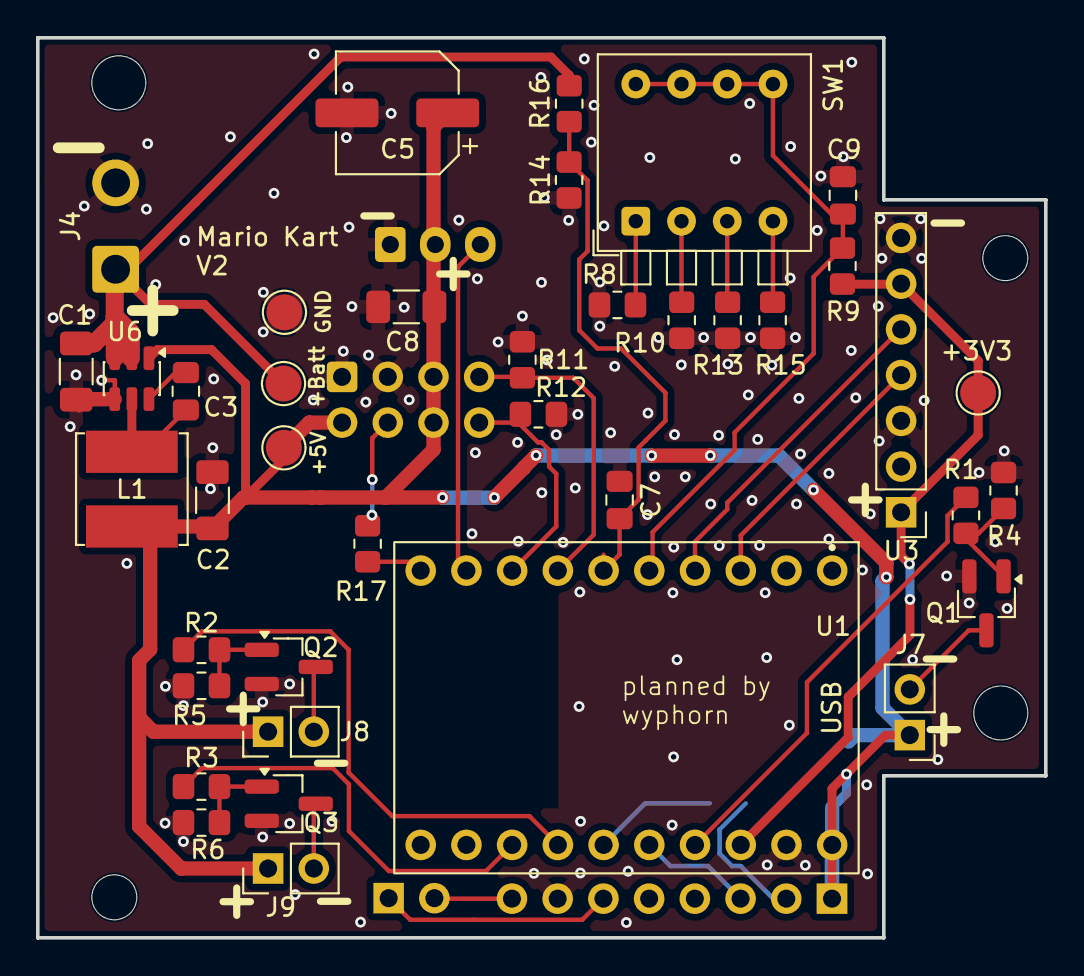
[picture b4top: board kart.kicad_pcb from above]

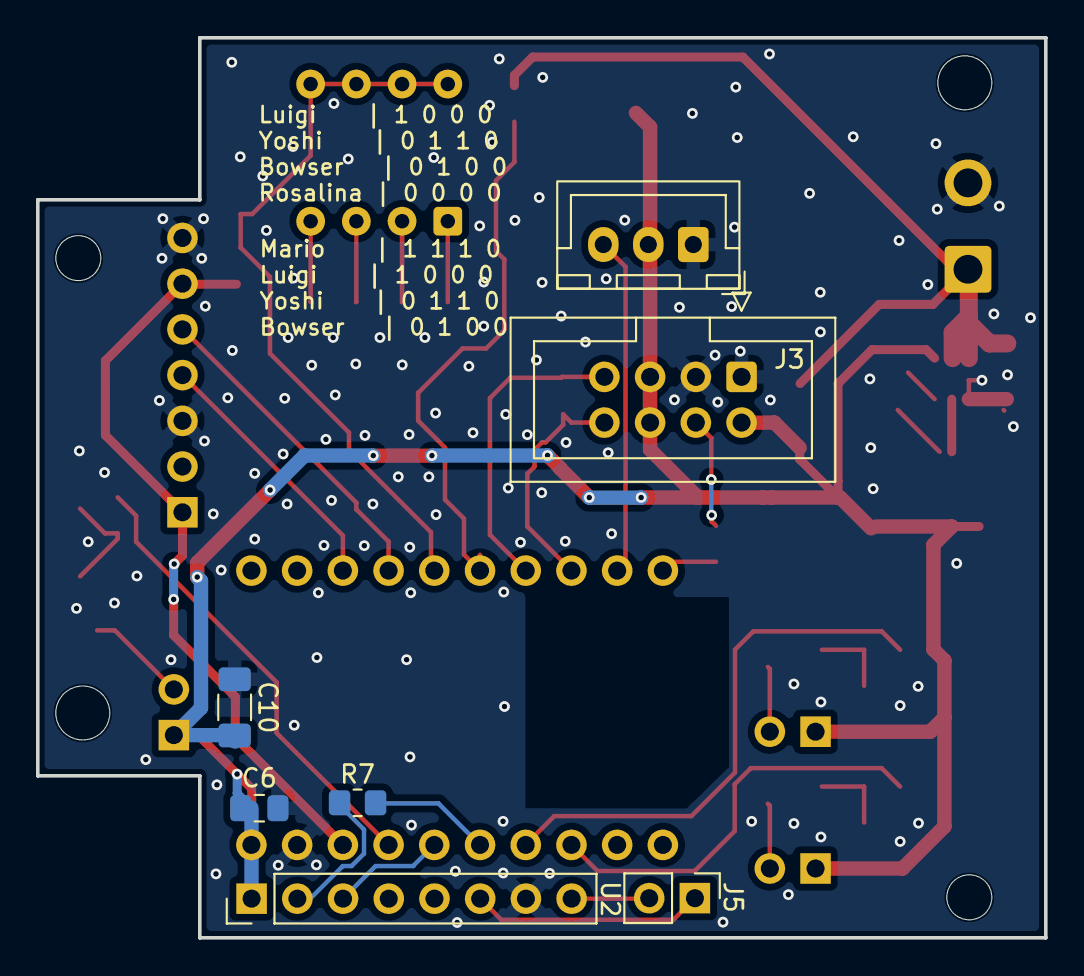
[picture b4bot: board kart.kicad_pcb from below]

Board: 2 copper layers, 56.0 x 50.0 mm, 46 parts (7 on the bottom side), 33 nets.

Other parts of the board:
+5V: +5V; TestPoint_Pad_D2.0mm
+Batt: +Batt; TestPoint_Pad_D2.0mm
GND: GND; TestPoint_Pad_D2.0mm

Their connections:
+5V: +5V.1 (1_1); also elsewhere on the board
+BATT: +Batt.1 (1_1); also elsewhere on the board
GND: GND.1 (1_1); also elsewhere on the board
